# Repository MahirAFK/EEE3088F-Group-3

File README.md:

# EEE3088F-Group-3 Micromouse project
Collaborators:<br />
Mahir Khan<br />
Nicholas Meehan

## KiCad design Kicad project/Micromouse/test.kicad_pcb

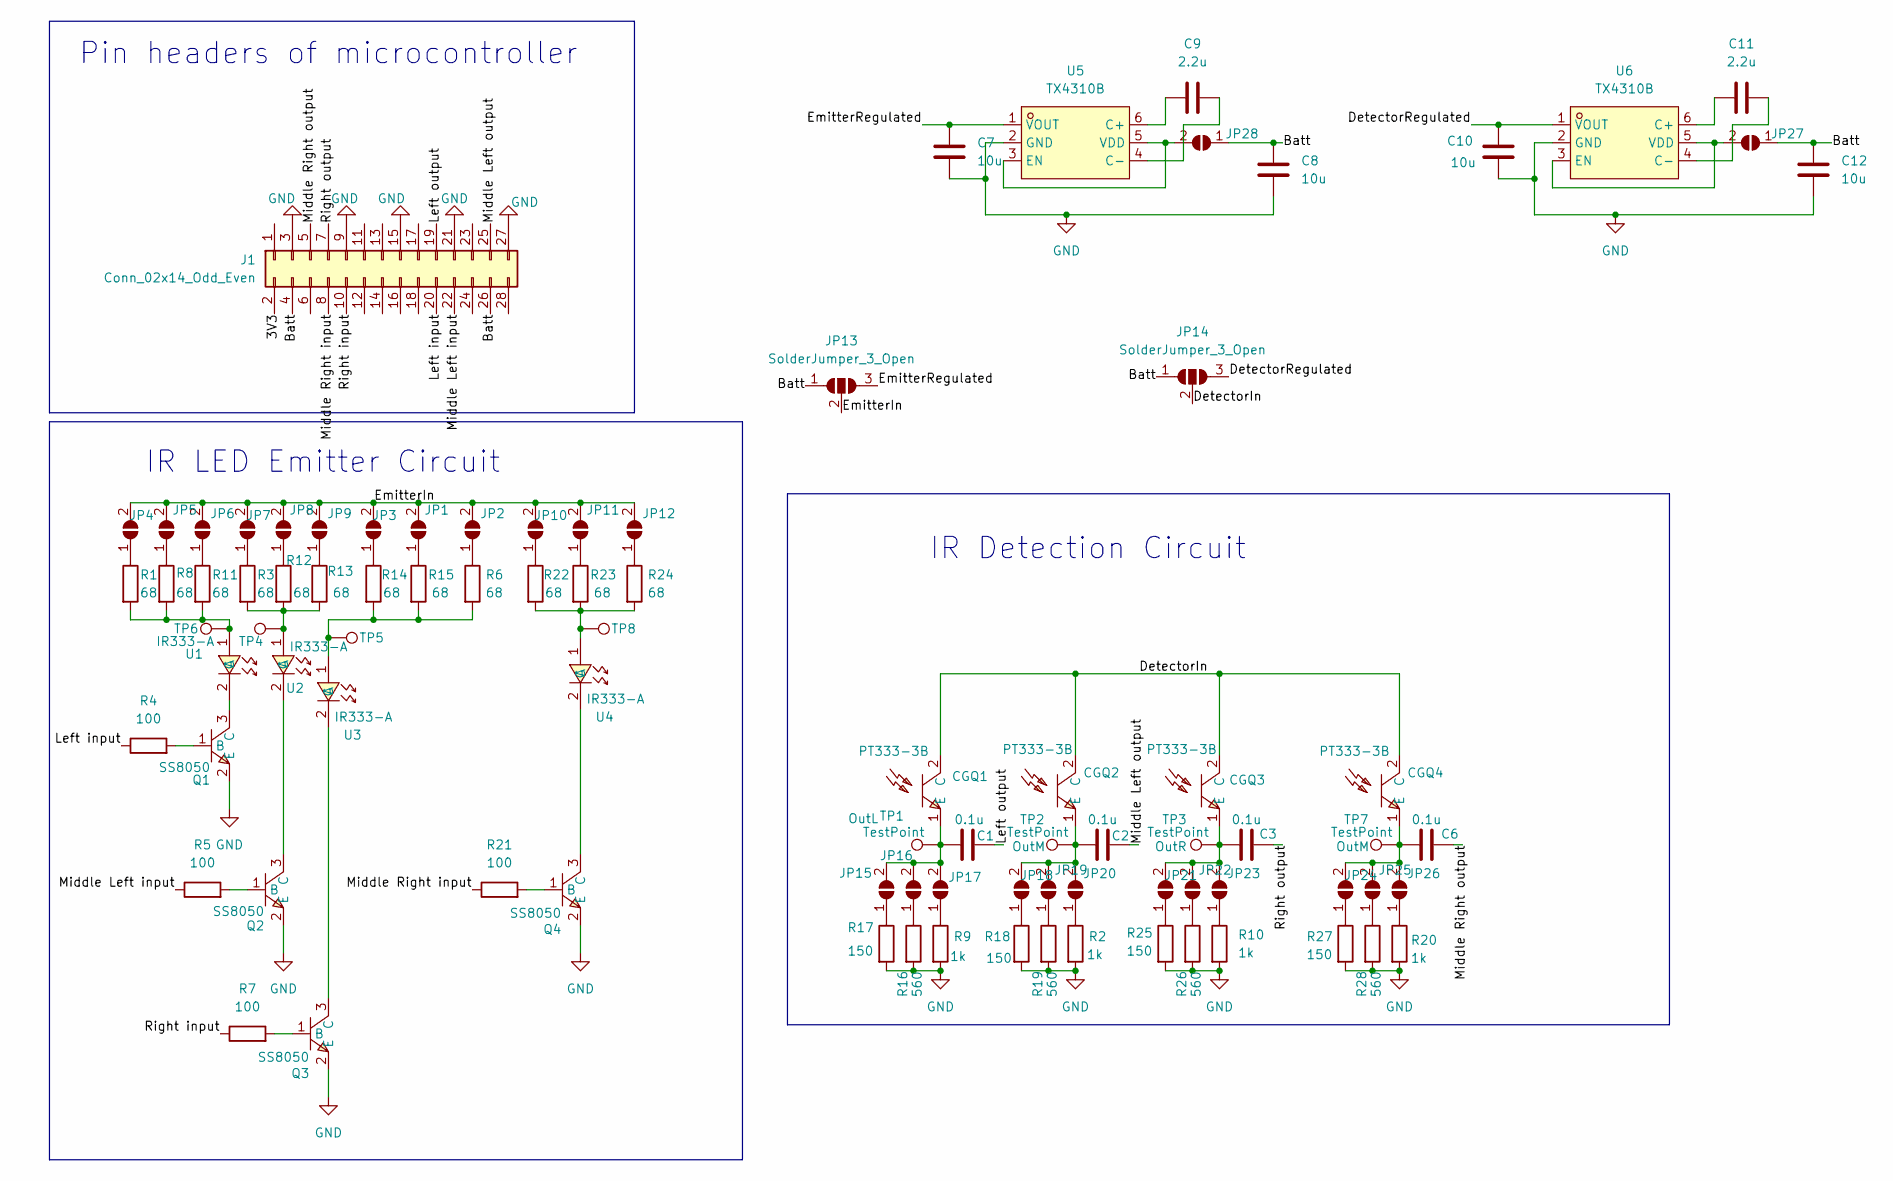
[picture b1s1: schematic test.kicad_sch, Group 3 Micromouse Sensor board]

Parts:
C1, C2, C3, C6: 0.1u; C0805
C7, C8, C10, C12: 10u; C0805
C9, C11: 2.2u; C0805
CGQ1, CGQ2, CGQ3, CGQ4: PT333-3B_C5134; LED_D5.0mm_Horizontal_O1.27mm_Z3.0mm; LCSC Part C5134
J1: Conn_02x14_Odd_Even; PinHeader_2x14_P2.54mm_Vertical
JP1, JP2, JP3, JP4, JP5, JP6, JP7, JP8, JP9, JP10, JP11, JP12, JP15, JP16, JP17, JP18, JP19, JP20, JP21, JP22, JP23, JP24, JP25, JP26, JP27, JP28: SolderJumper_2_Open; SolderJumper-2_P1.3mm_Open_RoundedPad1.0x1.5mm
JP13, JP14: SolderJumper_3_Open; SolderJumper-3_P2.0mm_Open_TrianglePad1.0x1.5mm
Q1, Q2, Q3, Q4: SS8050_C2150; SOT-23-3_L2.9-W1.3-P1.90-LS2.4-BR; LCSC Part C2150
R1, R3, R6, R8, R11, R12, R13, R14, R15, R22, R23, R24: 68; R_0805_2012Metric
R2, R9, R10, R20: 1k; R_0805_2012Metric
R4, R5, R7, R21: 100; R_0805_2012Metric
R16, R19, R26, R28: 560; R_0805_2012Metric
R17, R18, R25, R27: 150; R_0805_2012Metric
TP1, TP2, TP3, TP4, TP5, TP6, TP7, TP8: TestPoint; TestPoint_Pad_2.0x2.0mm
U1, U2, U3, U4: IR333-A_C264290; LED_D5.0mm_Horizontal_O1.27mm_Z3.0mm; LCSC Part C264290
U5, U6: TX4310B; SOT-23-6_L2.9-W1.6-P0.95-LS2.8-BR; LCSC Part C448640

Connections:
/3V3: J1.2
/Batt: C8.1, C12.1, J1.4, J1.26, JP13.1 (A), JP14.1 (A), JP27.1 (A), JP28.1 (A)
/DetectorIn: CGQ1.2 (C), CGQ2.2 (C), CGQ3.2 (C), CGQ4.2 (C), JP14.2 (C)
/DetectorRegulated: C10.1, JP14.3 (B), U6.1 (VOUT)
/EmitterIn: JP1.2 (B), JP2.2 (B), JP3.2 (B), JP4.2 (B), JP5.2 (B), JP6.2 (B), JP7.2 (B), JP8.2 (B), JP9.2 (B), JP10.2 (B), JP11.2 (B), JP12.2 (B), JP13.2 (C)
/EmitterRegulated: C7.1, JP13.3 (B), U5.1 (VOUT)
/Left input: J1.20, R4.1
/Left output: C1.2, J1.19
/Middle Left input: J1.22, R5.1
/Middle Left output: C2.2, J1.25
/Middle Right input: J1.8, R21.1
/Middle Right output: C6.2, J1.5
/Right input: J1.10, R7.1
/Right output: C3.2, J1.7
GND: C7.2, C8.2, C10.2, C12.2, J1.3, J1.9, J1.15, J1.21, J1.27, Q1.2 (E), Q2.2 (E), Q3.2 (E), Q4.2 (E), R2.2, R9.2, R10.2, R16.2, R17.2, R18.2, R19.2, R20.2, R25.2, R26.2, R27.2, R28.2, U5.2 (GND), U6.2 (GND)
unnamed: C1.1, CGQ1.1 (E), JP15.2 (B), JP16.2 (B), JP17.2 (B), TP1.1
unnamed: C2.1, CGQ2.1 (E), JP18.2 (B), JP19.2 (B), JP20.2 (B), TP2.1
unnamed: C3.1, CGQ3.1 (E), JP21.2 (B), JP22.2 (B), JP23.2 (B), TP3.1
unnamed: C6.1, CGQ4.1 (E), JP24.2 (B), JP25.2 (B), JP26.2 (B), TP7.1
unnamed: JP1.1 (A), R15.1
unnamed: JP2.1 (A), R6.1
unnamed: JP3.1 (A), R14.1
unnamed: JP4.1 (A), R1.1
unnamed: JP5.1 (A), R8.1
unnamed: JP6.1 (A), R11.1
unnamed: JP7.1 (A), R3.1
unnamed: JP8.1 (A), R12.1
unnamed: JP9.1 (A), R13.1
unnamed: JP10.1 (A), R22.1
unnamed: JP11.1 (A), R23.1
unnamed: JP12.1 (A), R24.1
unnamed: JP15.1 (A), R17.1
unnamed: JP16.1 (A), R16.1
unnamed: JP17.1 (A), R9.1
unnamed: JP18.1 (A), R18.1
unnamed: JP19.1 (A), R19.1
unnamed: JP20.1 (A), R2.1
unnamed: JP21.1 (A), R25.1
unnamed: JP22.1 (A), R26.1
unnamed: JP23.1 (A), R10.1
unnamed: JP24.1 (A), R27.1
unnamed: JP25.1 (A), R28.1
unnamed: JP26.1 (A), R20.1
unnamed: JP27.2 (B), U6.3 (EN), U6.5 (VDD)
unnamed: JP28.2 (B), U5.3 (EN), U5.5 (VDD)
unnamed: Q1.1 (B), R4.2
unnamed: Q1.3 (C), U1.2 (C)
unnamed: Q2.1 (B), R5.2
unnamed: Q2.3 (C), U2.2 (C)
unnamed: Q3.1 (B), R7.2
unnamed: Q3.3 (C), U3.2 (C)
unnamed: Q4.1 (B), R21.2
unnamed: Q4.3 (C), U4.2 (C)
unnamed: R1.2, R8.2, R11.2, TP6.1, U1.1 (A)
unnamed: R3.2, R12.2, R13.2, TP4.1, U2.1 (A)
unnamed: R6.2, R14.2, R15.2, TP5.1, U3.1 (A)
unnamed: R22.2, R23.2, R24.2, TP8.1, U4.1 (A)
unnamed: C9.2, U5.6 (C+)
unnamed: C9.1, U5.4 (C-)
unnamed: C11.2, U6.6 (C+)
unnamed: C11.1, U6.4 (C-)

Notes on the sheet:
Pin headers of microcontroller
IR Detection Circuit
IR LED Emitter Circuit

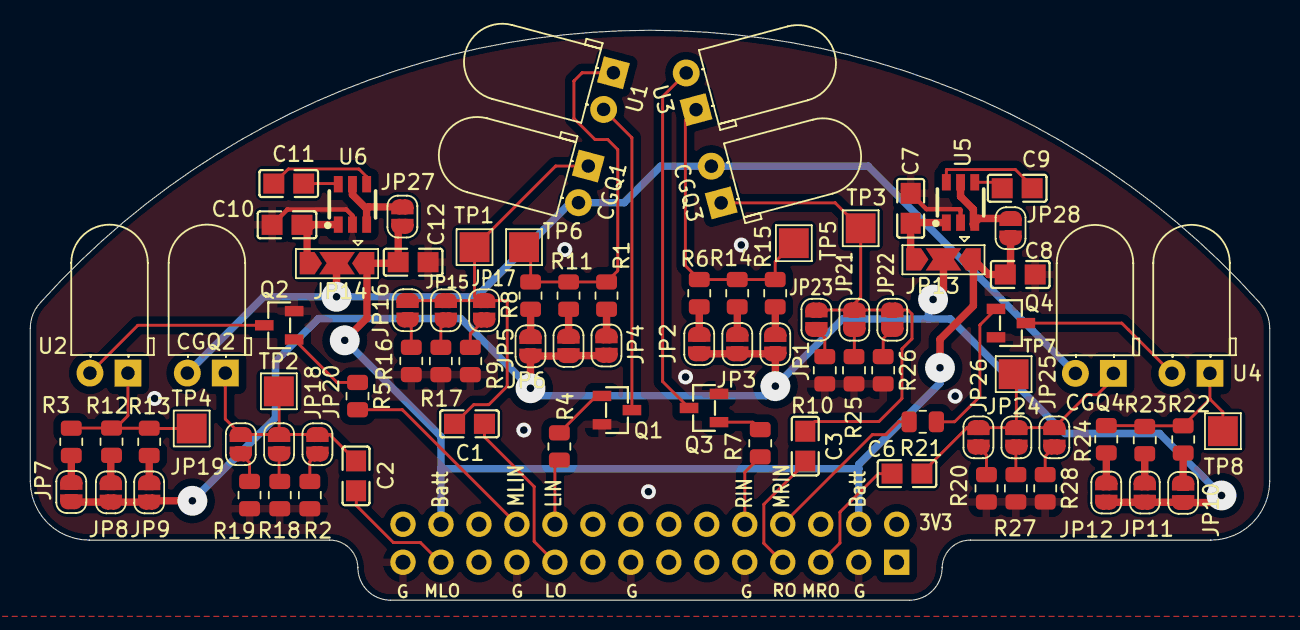
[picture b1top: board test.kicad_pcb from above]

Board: 2 copper layers, 82.9 x 38.1 mm, 89 parts (1 on the bottom side), 60 nets.

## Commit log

2024-03-13 Created README.md
2024-03-15 Updated Brief version
2024-03-17 Added LED and Photodiode datasheets
2024-03-21 Updated Brief
2024-03-21 Added BOM and cart screenshot
2024-03-23 Updated proof screenshots
2024-03-23 Added JLCPCB Tools Gerber files
2024-03-24 Renamed pngs and added kicad project files
